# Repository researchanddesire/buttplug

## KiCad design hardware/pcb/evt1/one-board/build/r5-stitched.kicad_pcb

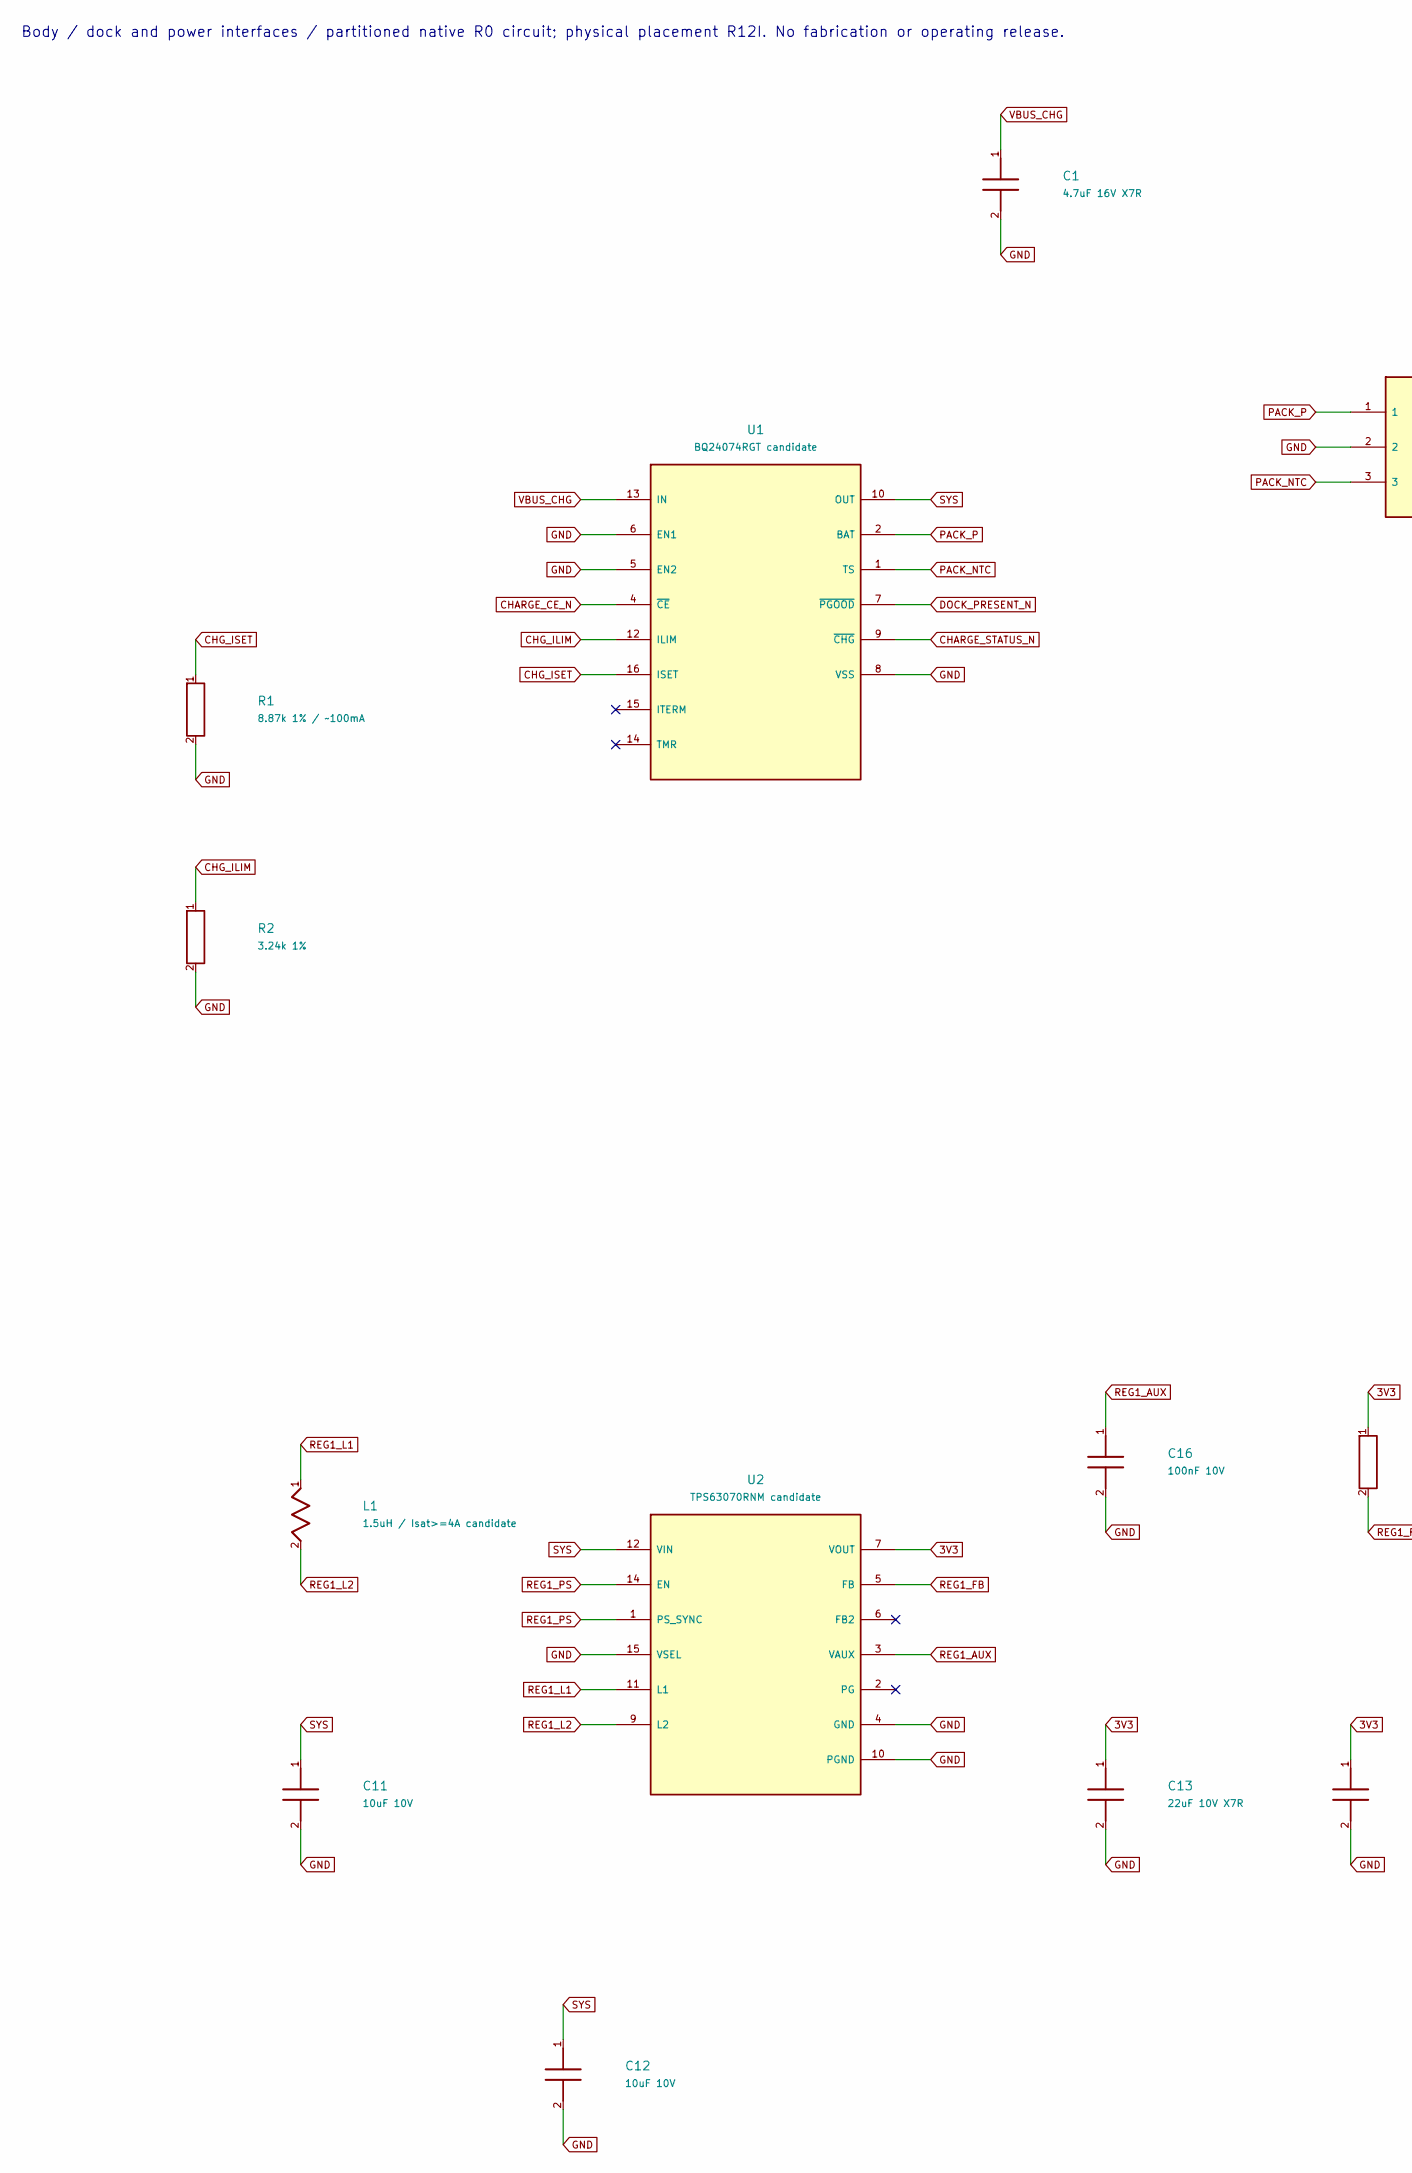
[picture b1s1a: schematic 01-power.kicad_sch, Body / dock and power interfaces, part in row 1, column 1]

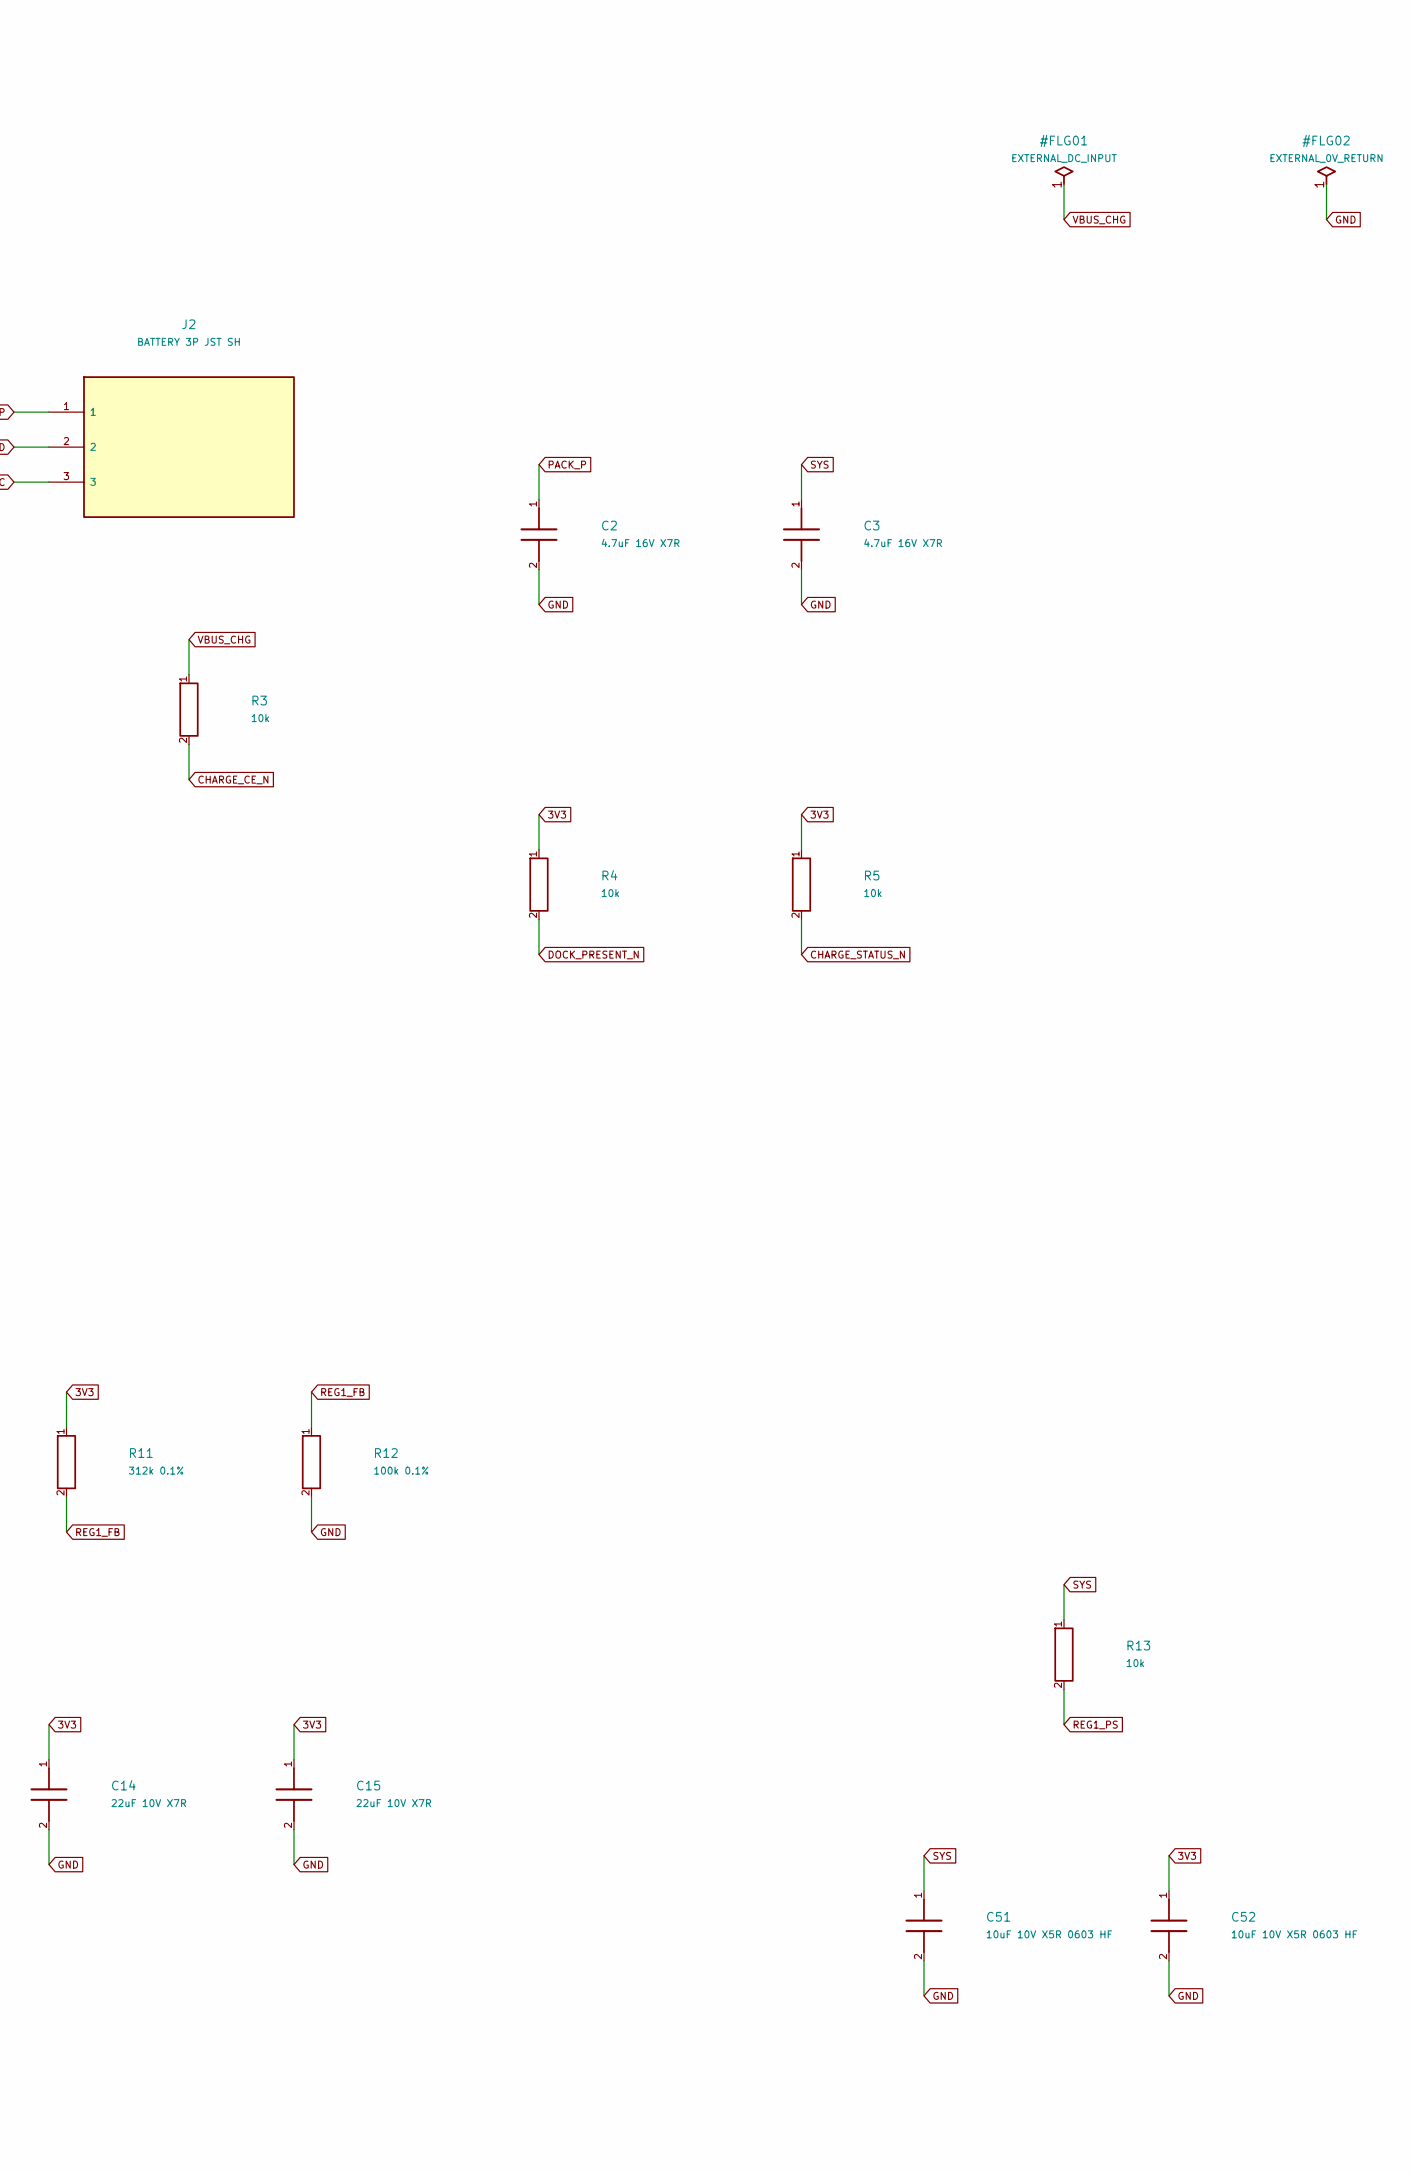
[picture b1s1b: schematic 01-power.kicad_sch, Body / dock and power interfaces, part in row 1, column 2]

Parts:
C1, C2, C3: 4.7uF 16V X7R; Murata_GRM21_0805_Reflow; Manufacturer Part Number GRM21BR71C475KE51L; LCSC Part Number C408144
C11, C12: 10uF 10V; Murata_GRM21_0805_Reflow
C13, C14, C15: 22uF 10V X7R; Murata_GRM31_1206_Reflow
C16: 100nF 10V; Murata_GRM18_0603_Reflow
C51, C52: 10uF 10V X5R 0603 HF; TDK_C1608_0603_Reflow; Manufacturer Part Number CL10A106KP8NNNC; LCSC Part Number C19702
J2: BATTERY 3P JST SH; JST_SH_SM03B-SRSS-TB_1x03-1MP_P1.00mm_Horizontal; Manufacturer Part Number SM03B-SRSS-TB(LF)(SN); LCSC Part Number C160403
L1: 1.5uH / Isat>=4A candidate; L_Coilcraft_XxL4020
R1: 8.87k 1% / ~100mA; R_0402_1005Metric; Manufacturer Part Number TC0210B8871TCC; LCSC Part Number C517790
R2: 3.24k 1%; R_0402_1005Metric; Manufacturer Part Number RT0402BRD073K24L; LCSC Part Number C852760
R3, R4, R5: 10k; R_0402_1005Metric
R11: 312k 0.1%; Vishay_TNPW0603_IEC_Reflow; Manufacturer Part Number RT0603BRD07312KL; LCSC Part Number C861315
R12: 100k 0.1%; Vishay_TNPW0603_IEC_Reflow
R13: 10k; Vishay_TNPW0603_IEC_Reflow
U1: BQ24074RGT candidate; TI_RGT0016C_3x3mm_BQ24074_EP1.68mm
U2: TPS63070RNM candidate; TI_RNM0015A_2.5x3mm_TPS63070

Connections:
3V3: C13.1, C14.1, C15.1, C52.1, R4.1, R5.1, R11.1, U2.7 (VOUT), U2.8 (VOUT); also elsewhere on the board
CHARGE_CE_N: R3.2, U1.4 (~CE); also elsewhere on the board
CHARGE_STATUS_N: R5.2, U1.9 (~CHG)
CHG_ILIM: R2.1, U1.12 (ILIM)
CHG_ISET: R1.1, U1.16 (ISET)
DOCK_PRESENT_N: R4.2, U1.7 (~PGOOD); also elsewhere on the board
GND: C1.2, C2.2, C3.2, C11.2, C12.2, C13.2, C14.2, C15.2, C16.2, C51.2, C52.2, J2.2, R1.2, R2.2, R12.2, U1.5 (EN2), U1.6 (EN1), U1.8 (VSS), U1.17 (EP), U2.4 (GND), U2.10 (PGND), U2.15 (VSEL); also elsewhere on the board
PACK_NTC: J2.3, U1.1 (TS)
PACK_P: C2.1, J2.1, U1.2 (BAT), U1.3 (BAT); also elsewhere on the board
REG1_AUX: C16.1, U2.3 (VAUX)
REG1_FB: R11.2, R12.1, U2.5 (FB)
REG1_L1: L1.1, U2.11 (L1)
REG1_L2: L1.2, U2.9 (L2)
REG1_PS: R13.2, U2.1 (PS_SYNC), U2.14 (EN)
SYS: C3.1, C11.1, C12.1, C51.1, R13.1, U1.10 (OUT), U1.11 (OUT), U2.12 (VIN), U2.13 (VIN); also elsewhere on the board
VBUS_CHG: C1.1, R3.1, U1.13 (IN); also elsewhere on the board

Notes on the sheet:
Body / dock and power interfaces / partitioned native R0 circuit; physical placement R12I. No fabrication or operating release.

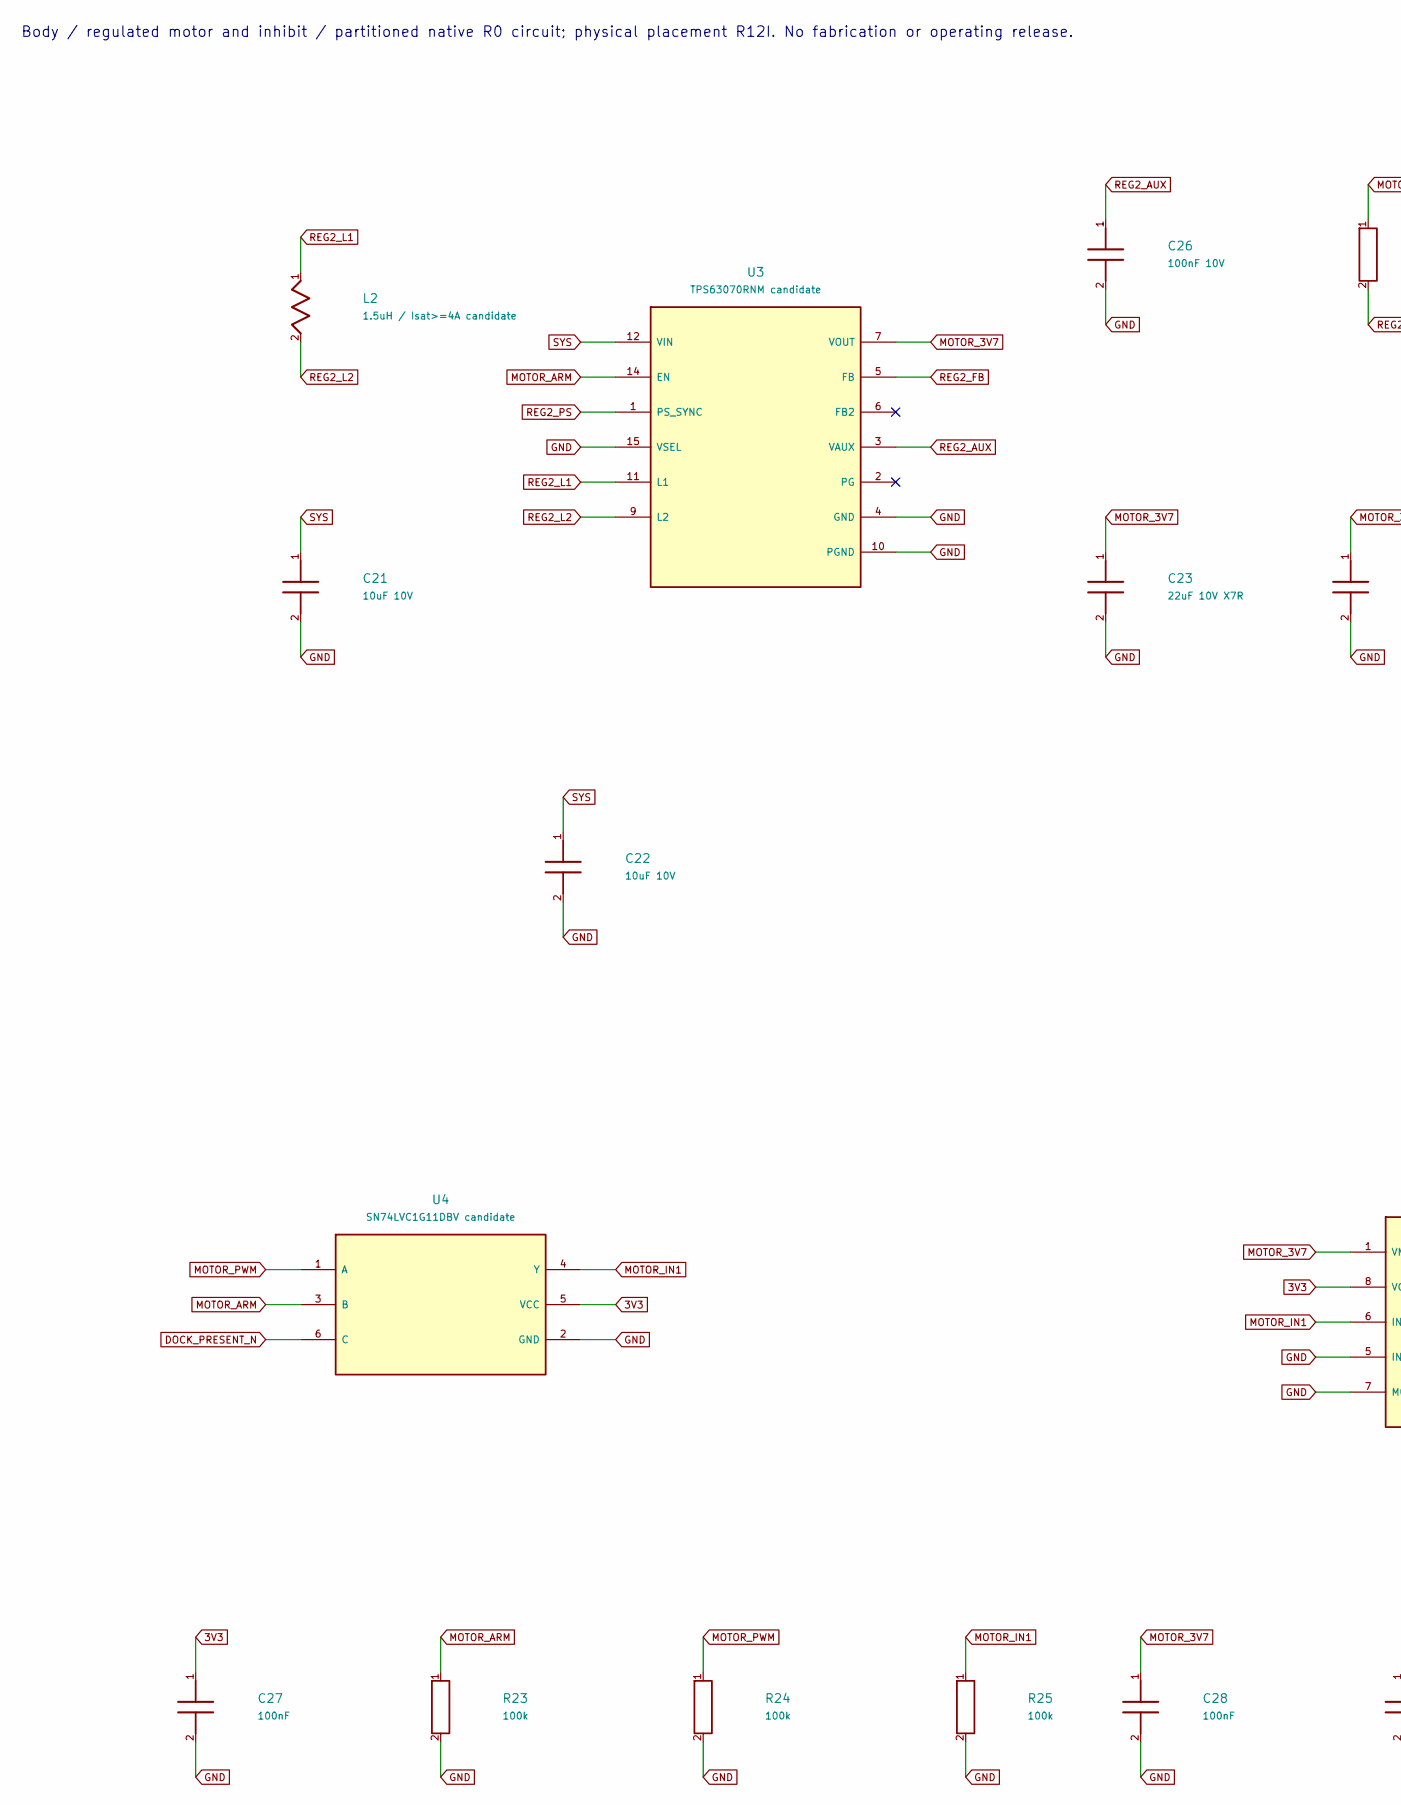
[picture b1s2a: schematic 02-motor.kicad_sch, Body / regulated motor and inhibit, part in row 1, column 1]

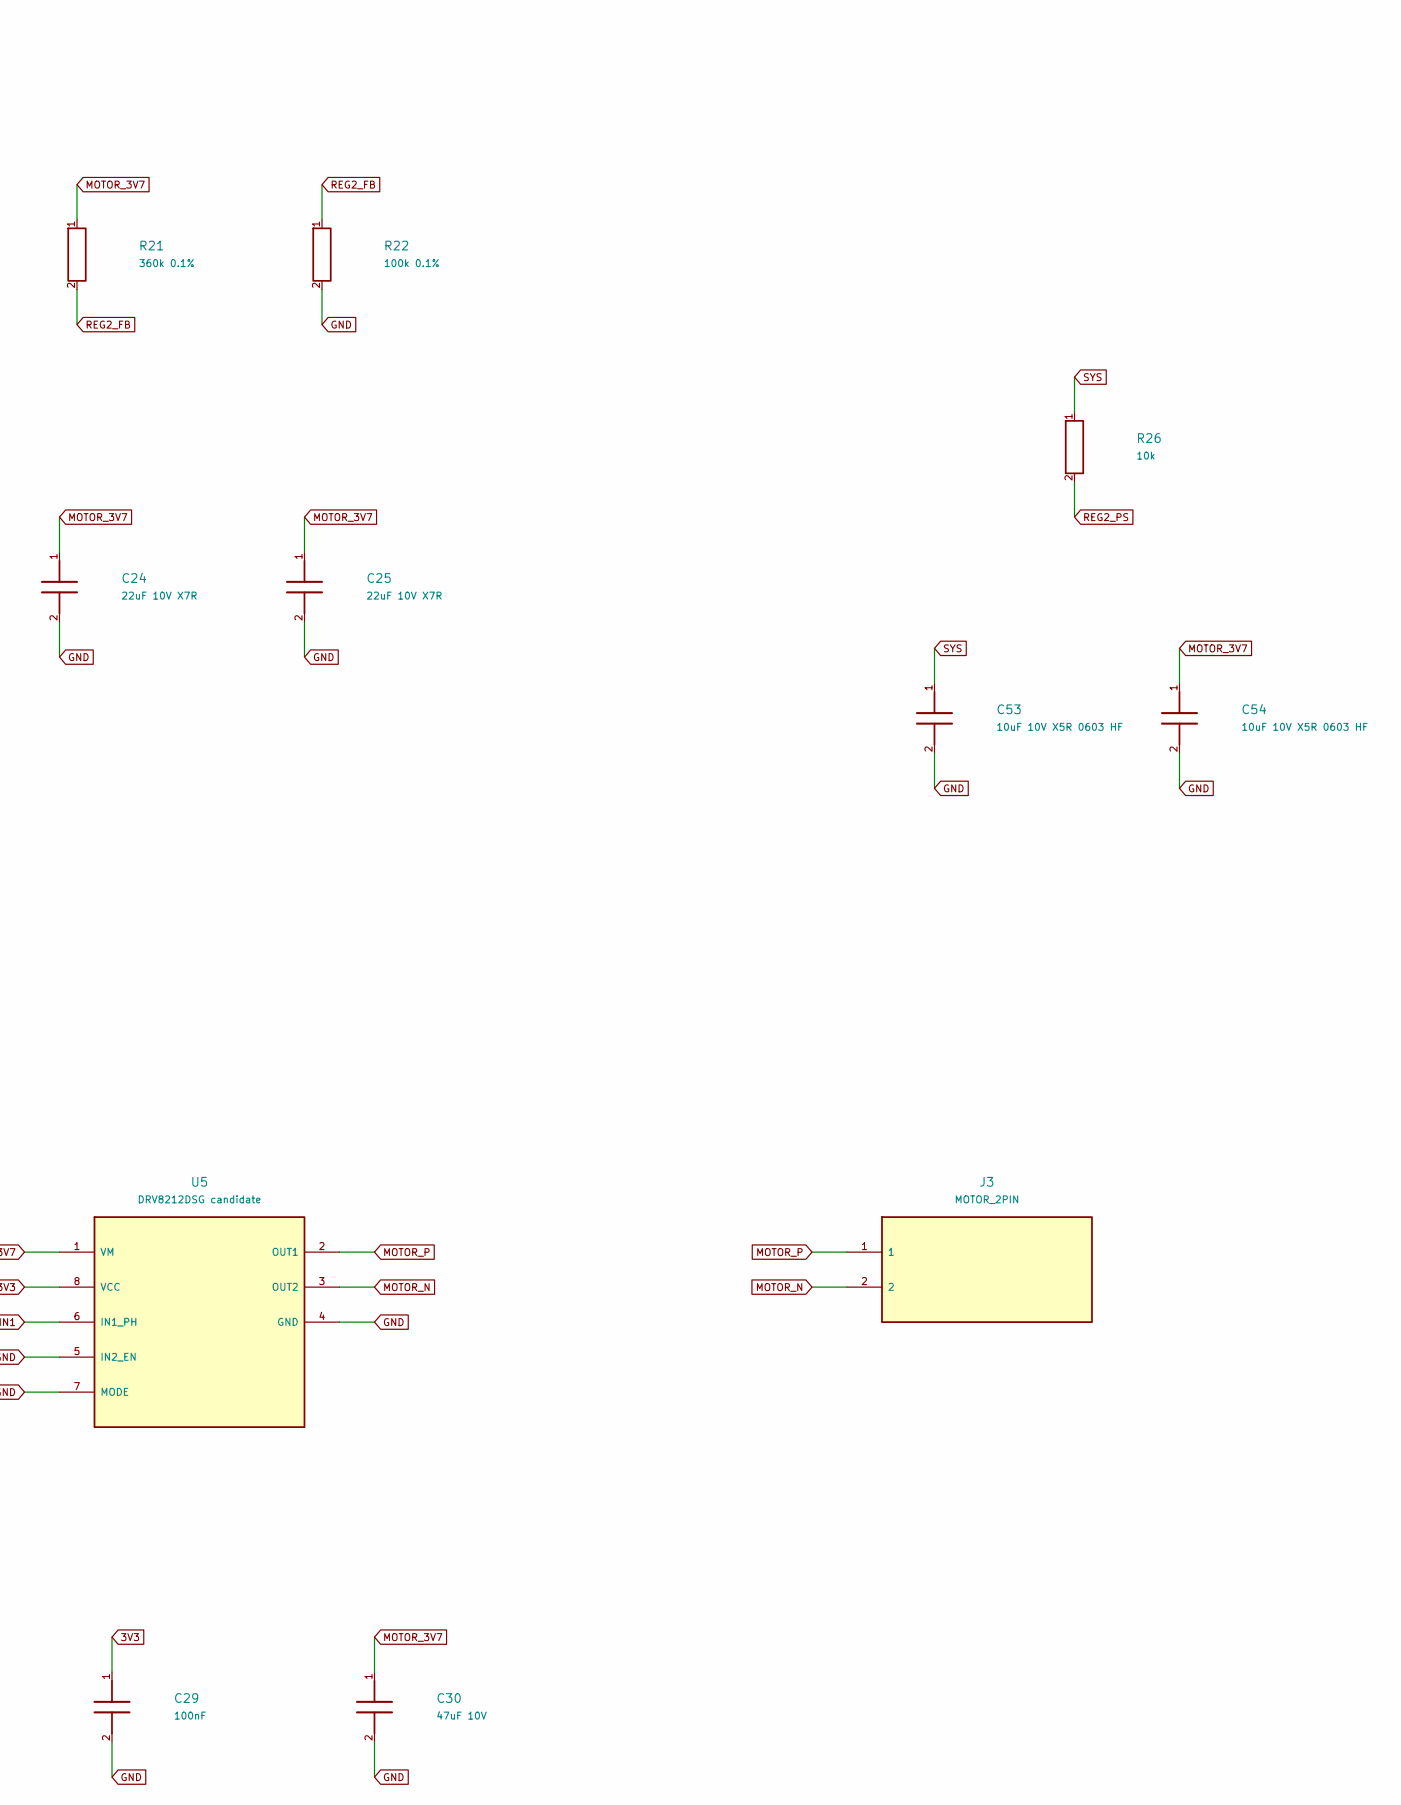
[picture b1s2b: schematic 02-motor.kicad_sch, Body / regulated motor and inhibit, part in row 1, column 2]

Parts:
C21, C22: 10uF 10V; Murata_GRM21_0805_Reflow
C23, C24, C25: 22uF 10V X7R; Murata_GRM31_1206_Reflow
C26: 100nF 10V; Murata_GRM18_0603_Reflow
C27: 100nF; Murata_GRM18_0603_Reflow
C28, C29: 100nF; C_0402_1005Metric
C30: 47uF 10V; Murata_GRM32_1210_Reflow
C53, C54: 10uF 10V X5R 0603 HF; TDK_C1608_0603_Reflow; Manufacturer Part Number CL10A106KP8NNNC; LCSC Part Number C19702
J3: MOTOR_2PIN; JST_SH_SM02B-SRSS-TB_1x02-1MP_P1.00mm_Horizontal
L2: 1.5uH / Isat>=4A candidate; L_Coilcraft_XxL4020
R21: 360k 0.1%; RESI_PTFR0805_C16003; Manufacturer Part Number PTFR0805B360KN9; LCSC Part Number C351576
R22: 100k 0.1%; Vishay_TNPW0603_IEC_Reflow
R23, R24, R25: 100k; R_0402_1005Metric
R26: 10k; Vishay_TNPW0603_IEC_Reflow
U3: TPS63070RNM candidate; TI_RNM0015A_2.5x3mm_TPS63070
U4: SN74LVC1G11DBV candidate; SOT-23-6
U5: DRV8212DSG candidate; WSON-8-1EP_2x2mm_P0.5mm_EP0.9x1.6mm

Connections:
3V3: C27.1, C29.1, U4.5 (VCC), U5.8 (VCC); also elsewhere on the board
DOCK_PRESENT_N: U4.6 (C); also elsewhere on the board
GND: C21.2, C22.2, C23.2, C24.2, C25.2, C26.2, C27.2, C28.2, C29.2, C30.2, C53.2, C54.2, R22.2, R23.2, R24.2, R25.2, U3.4 (GND), U3.10 (PGND), U3.15 (VSEL), U4.2 (GND), U5.4 (GND), U5.5 (IN2_EN), U5.7 (MODE), U5.9 (EP); also elsewhere on the board
MOTOR_3V7: C23.1, C24.1, C25.1, C28.1, C30.1, C54.1, R21.1, U3.7 (VOUT), U3.8 (VOUT), U5.1 (VM)
MOTOR_ARM: R23.1, U3.14 (EN), U4.3 (B); also elsewhere on the board
MOTOR_IN1: R25.1, U4.4 (Y), U5.6 (IN1_PH)
MOTOR_N: J3.2, U5.3 (OUT2)
MOTOR_P: J3.1, U5.2 (OUT1)
MOTOR_PWM: R24.1, U4.1 (A); also elsewhere on the board
REG2_AUX: C26.1, U3.3 (VAUX)
REG2_FB: R21.2, R22.1, U3.5 (FB)
REG2_L1: L2.1, U3.11 (L1)
REG2_L2: L2.2, U3.9 (L2)
REG2_PS: R26.2, U3.1 (PS_SYNC)
SYS: C21.1, C22.1, C53.1, R26.1, U3.12 (VIN), U3.13 (VIN); also elsewhere on the board

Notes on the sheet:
Body / regulated motor and inhibit / partitioned native R0 circuit; physical placement R12I. No fabrication or operating release.

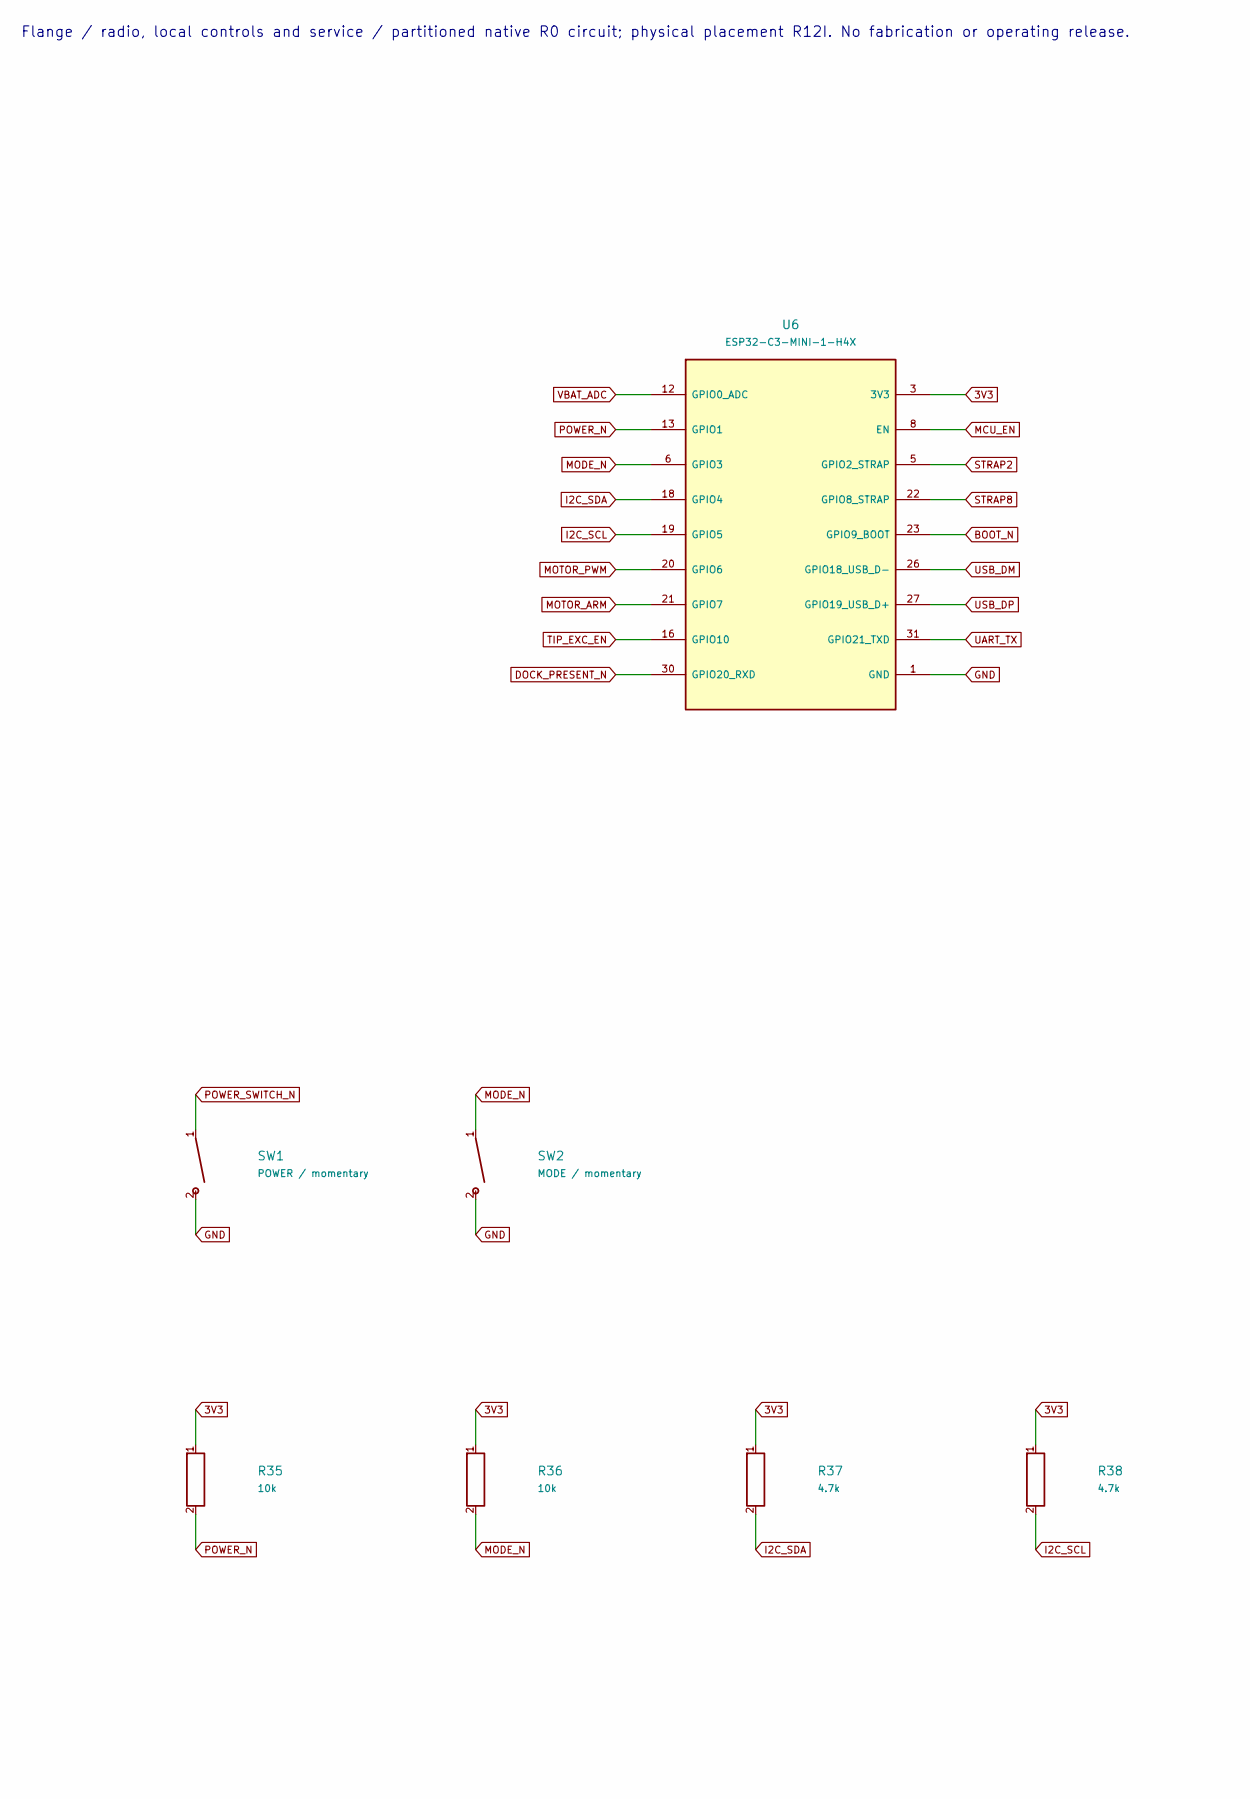
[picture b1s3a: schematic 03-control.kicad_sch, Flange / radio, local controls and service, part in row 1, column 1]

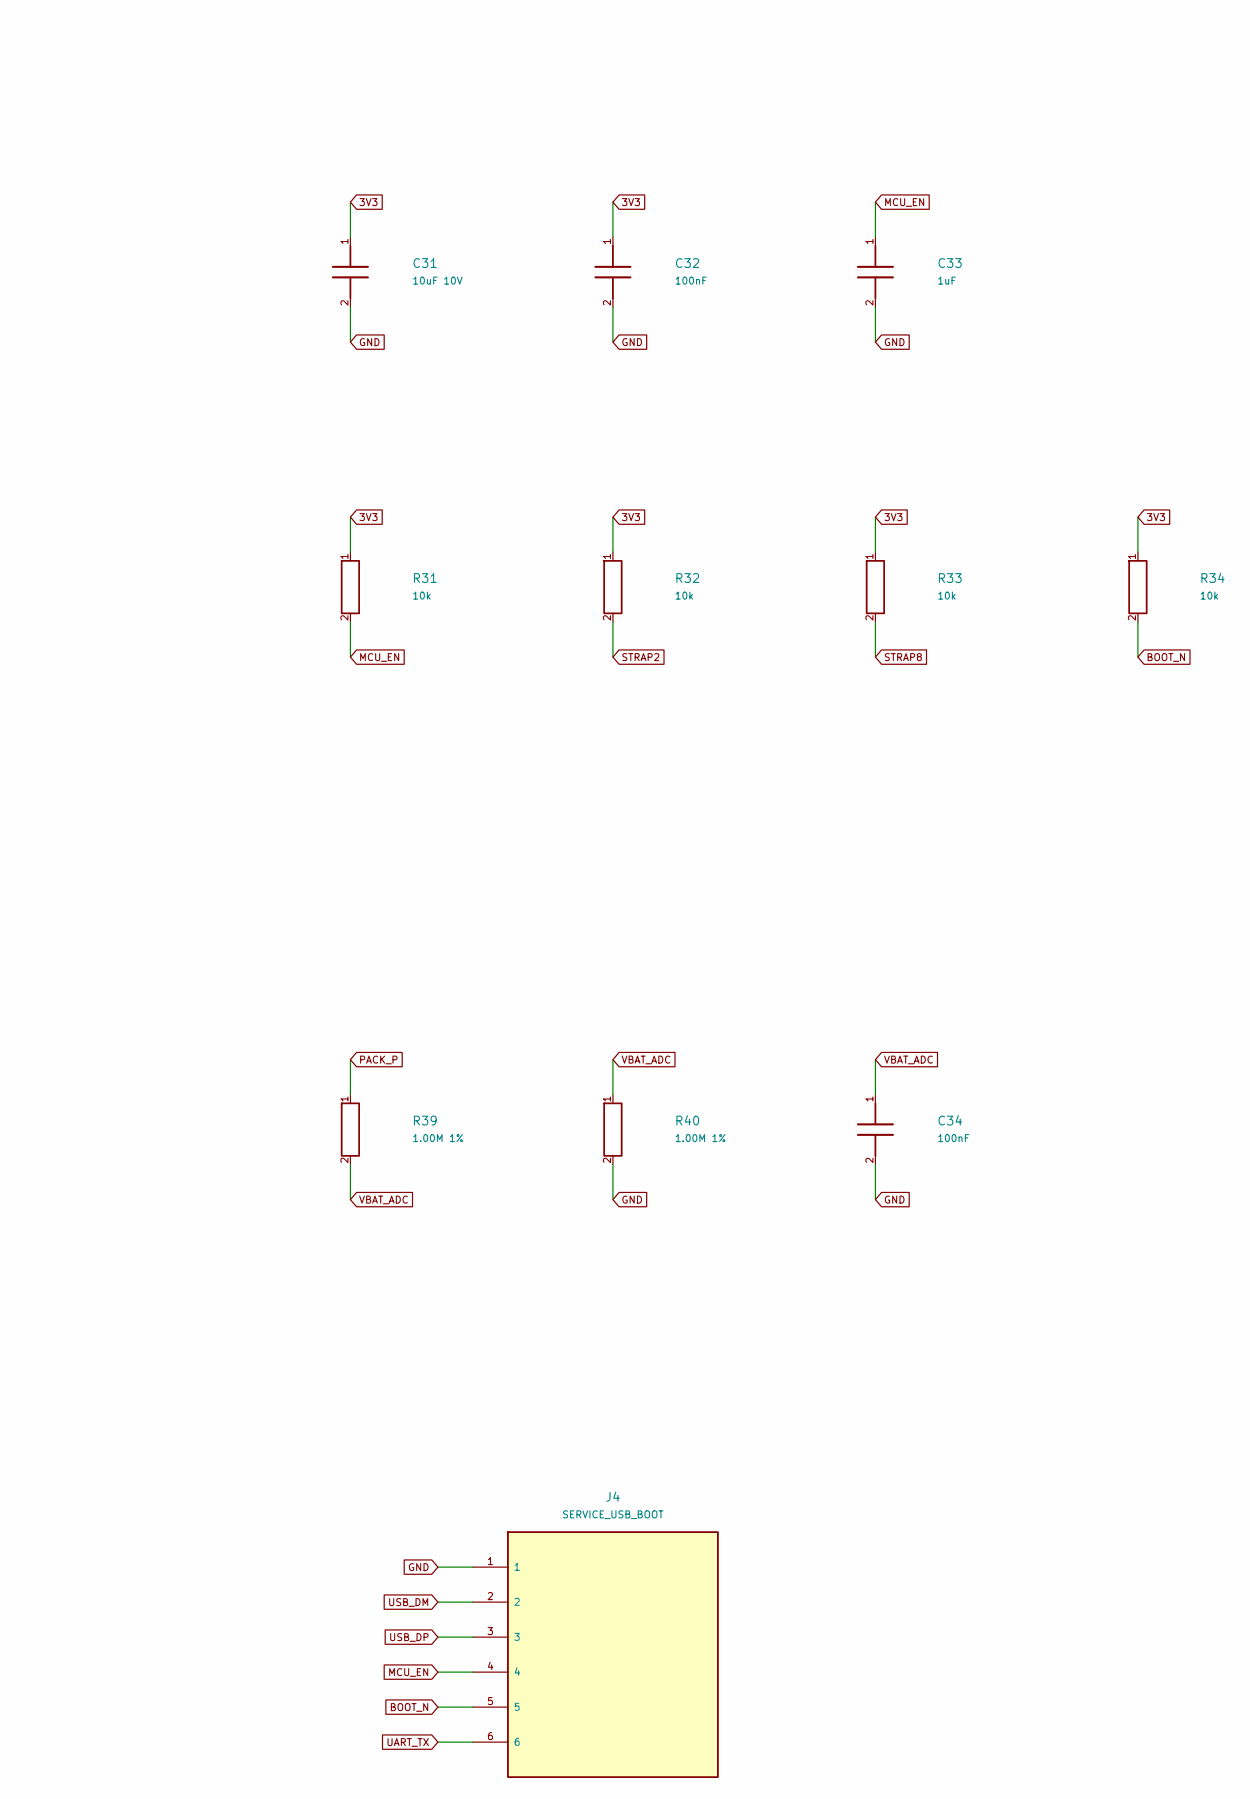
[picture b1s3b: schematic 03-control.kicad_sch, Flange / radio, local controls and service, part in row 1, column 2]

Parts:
C31: 10uF 10V; Murata_GRM21_0805_Reflow
C32, C34: 100nF; Murata_GRM18_0603_Reflow
C33: 1uF; TDK_C1608_0603_Reflow; Manufacturer Part Number CGA3E1X7R1V105KT000N; LCSC Part Number C342956
J4: SERVICE_USB_BOOT; JST_SH_SM06B-SRSS-TB_1x06-1MP_P1.00mm_Horizontal
R31, R32, R33, R34, R35, R36: 10k; Vishay_TNPW0603_IEC_Reflow
R37, R38: 4.7k; Vishay_TNPW0603_IEC_Reflow
R39, R40: 1.00M 1%; Vishay_TNPW0805_IEC_Reflow
SW1: POWER / momentary; SW_SPST_B3U-1000P
SW2: MODE / momentary; SW_SPST_B3U-1000P
U6: ESP32-C3-MINI-1-H4X; Espressif_ESP32-C3-MINI-1_53Pads; Manufacturer Part Number ESP32-C3-MINI-1-H4X; LCSC Part Number C41349510

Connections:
3V3: C31.1, C32.1, R31.1, R32.1, R33.1, R34.1, R35.1, R36.1, R37.1, R38.1, U6.3 (3V3); also elsewhere on the board
BOOT_N: J4.5, R34.2, U6.23 (GPIO9_BOOT); also elsewhere on the board
DOCK_PRESENT_N: U6.30 (GPIO20_RXD); also elsewhere on the board
GND: C31.2, C32.2, C33.2, C34.2, J4.1, R40.2, SW1.2, SW2.2, U6.1 (GND), U6.2 (GND), U6.11 (GND), U6.14 (GND), U6.36 (GND), U6.37 (GND), U6.38 (GND), U6.39 (GND), U6.40 (GND), U6.41 (GND), U6.42 (GND), U6.43 (GND), U6.44 (GND), U6.45 (GND), U6.46 (GND), U6.47 (GND), U6.48 (GND), U6.49 (GND), U6.50 (GND), U6.51 (GND), U6.52 (GND), U6.53 (GND); also elsewhere on the board
I2C_SCL: R38.2, U6.19 (GPIO5); also elsewhere on the board
I2C_SDA: R37.2, U6.18 (GPIO4); also elsewhere on the board
MCU_EN: C33.1, J4.4, R31.2, U6.8 (EN); also elsewhere on the board
MODE_N: R36.2, SW2.1, U6.6 (GPIO3); also elsewhere on the board
MOTOR_ARM: U6.21 (GPIO7); also elsewhere on the board
MOTOR_PWM: U6.20 (GPIO6); also elsewhere on the board
PACK_P: R39.1; also elsewhere on the board
POWER_N: R35.2, U6.13 (GPIO1); also elsewhere on the board
POWER_SWITCH_N: SW1.1; also elsewhere on the board
STRAP2: R32.2, U6.5 (GPIO2_STRAP)
STRAP8: R33.2, U6.22 (GPIO8_STRAP)
UART_TX: J4.6, U6.31 (GPIO21_TXD)
USB_DM: J4.2, U6.26 (GPIO18_USB_D-); also elsewhere on the board
USB_DP: J4.3, U6.27 (GPIO19_USB_D+); also elsewhere on the board
VBAT_ADC: C34.1, R39.2, R40.1, U6.12 (GPIO0_ADC)

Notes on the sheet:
Flange / radio, local controls and service / partitioned native R0 circuit; physical placement R12I. No fabrication or operating release.
